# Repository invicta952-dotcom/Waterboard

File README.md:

# Waterboard
#   what is this?
this is really basic devboard with bare minmum features. it has 50 pins in total. It has an memory of 16 mb. The mcu used in this rp2040. It can only be used in simple task. It  has usb-c for flashing your firmware. It has 24 gipo pins. It has built in-clock of 12mHz

#   how to use this??
just connect the devboard with your computer and flash the code and enjoy.

#  how to assemble?
i wouldnt recommend this to you if u are an begineer, instead get it pcba
#    pcba
1) dowload the geber file from repo
2) go to jlcpcb or any other pcb service provider
3) upload the gerber
4) scroll down and select pcba
5) order it
6) enjoy

#    pcb
1) same as pcba till 3 step
2) order the pcb without pcba
3) order the components given in BOM
4) solder all the components on pcb using hot plate

#   schnematics overview

<br>
i know the schnematics is kind of messy but it is what it is

#   pcb

<br>
there are many shape i could have taken but i decided to go with dolphine because i wanted it to resemble something from minecraft which is one of my favourite game.

#   3D view

<br> 
the board kinda looks empty because i cant find cool silkscreen
<br>
<br>
#   zine

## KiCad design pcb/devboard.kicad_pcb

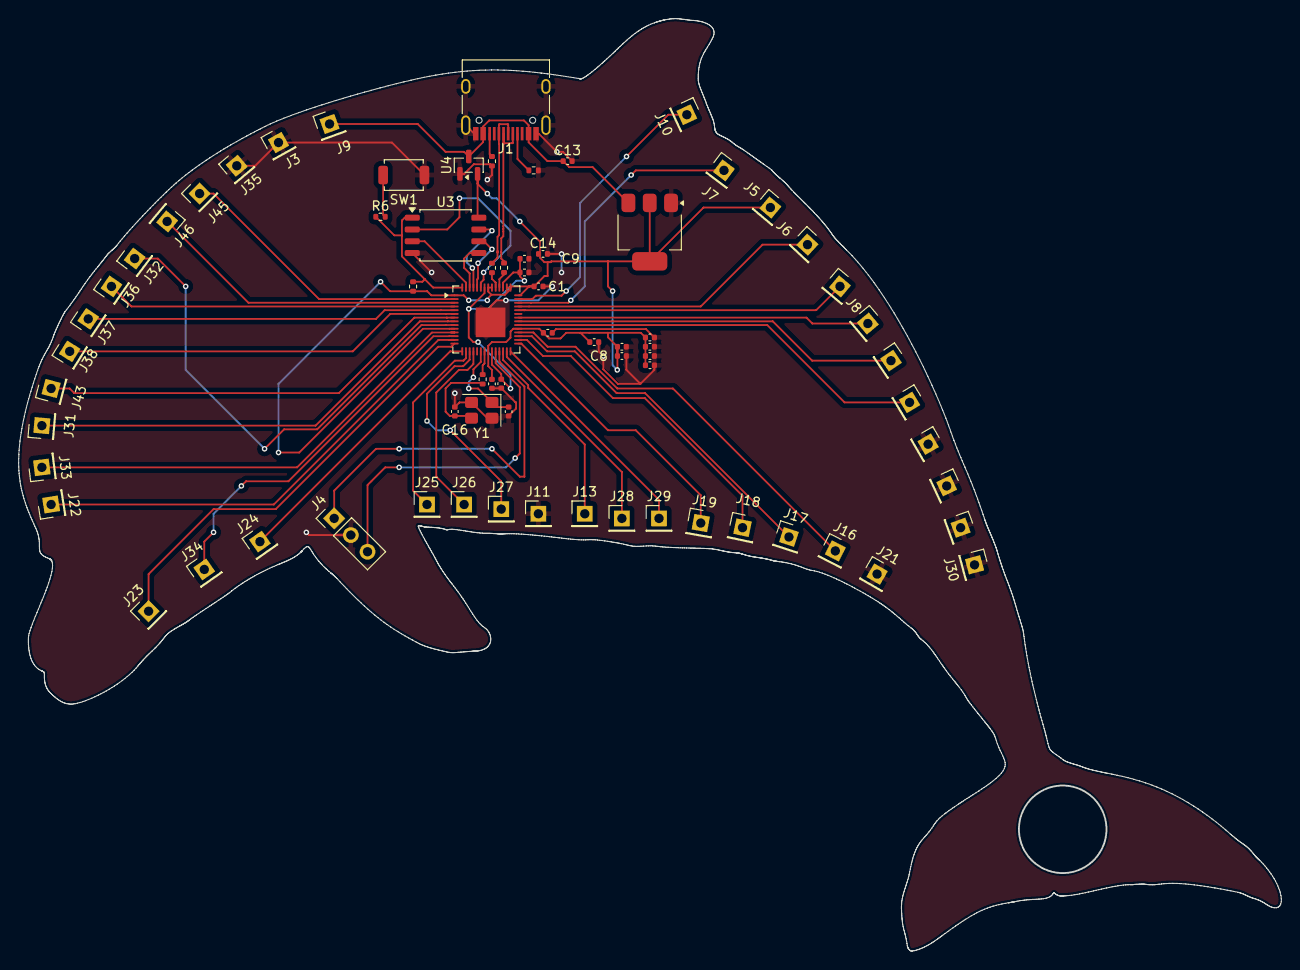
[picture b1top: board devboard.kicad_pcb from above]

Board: 2 copper layers, 135.9 x 100.3 mm, 72 parts (0 on the bottom side), 52 nets.

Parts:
C1, C2, C3, C4, C5, C6, C7, C8, C11, C12, C17: 0.1uF; C_0402_1005Metric
C9, C10: 1uF; C_0402_1005Metric
C13, C14: 10uF; C_0402_1005Metric
C15, C16: 33pF; C_0402_1005Metric
J1: USB_C_Receptacle_USB2.0_14P; USB_C_Receptacle_HRO_TYPE-C-31-M-12
J2, J3, J5, J6, J7, J8, J9, J10, J11, J12, J13, J14, J15, J16, J17, J18, J19, J20, J21, J22, J23, J24, J25, J26, J27, J28, J29, J30, J31, J32, J33, J34, J35, J36, J37, J38, J43, J44, J45, J46: Conn_01x01_Pin; PinHeader_1x01_P2.54mm_Vertical
J4: Conn_01x03_Pin; PinHeader_1x03_P2.54mm_Vertical
R1, R2: 5.1K; R_0402_1005Metric
R3, R4: 27; R_0402_1005Metric
R5, R6: 1K; R_0402_1005Metric
R7: 10K; R_0402_1005Metric
SW1: SW_Push; SW_SPST_TS-1088-xR020
U1: RP2040; QFN-56-1EP_7x7mm_P0.4mm_EP3.2x3.2mm
U2: NCP1117-3.3_SOT223; SOT-223-3_TabPin2
U3: W25Q128JVS; SOIC-8_5.3x5.3mm_P1.27mm
U4: MCP1700x-330xxTT; SOT-23
Y1: 12 MHz; Crystal_SMD_3225-4Pin_3.2x2.5mm

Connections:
+1V1: C9.1, C11.1, C12.1, U1.23 (DVDD), U1.45 (VREG_VOUT), U1.50 (DVDD)
+3V3: C1.1, C2.1, C3.1, C4.1, C5.1, C6.1, C7.1, C8.1, C10.1, C14.1, C17.2, J5.1, R7.1, U1.1 (IOVDD), U1.10 (IOVDD), U1.22 (IOVDD), U1.33 (IOVDD), U1.42 (IOVDD), U1.43 (ADC_AVDD), U1.44 (VREG_VIN), U1.48 (USB_VDD), U1.49 (IOVDD), U2.2 (VO), U3.8 (VCC), U4.2 (VO)
GIPO0: J45.1, U1.2 (GPIO0)
GIPO1: J46.1, U1.3 (GPIO1)
GIPO2: J36.1, U1.4 (GPIO2)
GIPO3: J37.1, U1.5 (GPIO3)
GIPO4: J38.1, U1.6 (GPIO4)
GIPO5: J43.1, U1.7 (GPIO5)
GIPO6: J31.1, U1.8 (GPIO6)
GIPO7: J32.1, U1.9 (GPIO7)
GIPO8: J33.1, U1.11 (GPIO8)
GIPO9: J34.1, U1.12 (GPIO9)
GIPO10: J22.1, U1.13 (GPIO10)
GIPO11: J23.1, U1.14 (GPIO11)
GIPO12: J24.1, U1.15 (GPIO12)
GIPO13: J25.1, U1.16 (GPIO13)
GIPO14: J27.1, U1.17 (GPIO14)
GIPO15: J26.1, U1.18 (GPIO15)
GIPO16: J28.1, U1.27 (GPIO16)
GIPO17: J29.1, U1.28 (GPIO17)
GIPO18: J19.1, U1.29 (GPIO18)
GIPO19: J18.1, U1.30 (GPIO19)
GIPO20: J17.1, U1.31 (GPIO20)
GIPO21: J16.1, U1.32 (GPIO21)
GIPO22: J14.1, U1.34 (GPIO22)
GIPO23: J12.1, U1.35 (GPIO23)
GIPO24: J8.1, U1.36 (GPIO24)
GIPO_ABC0: J2.1, U1.38 (GPIO26/ADC0)
GIPO_ABC1: J6.1, U1.39 (GPIO27/ADC1)
GIPO_ABC2: J7.1, U1.40 (GPIO28/ADC2)
GIPO_ABC3: J10.1, U1.41 (GPIO29/ADC3)
GND: C1.2, C2.2, C3.2, C4.2, C5.2, C6.2, C7.2, C8.2, C9.2, C10.2, C11.2, C12.2, C13.2, C14.2, C15.2, C16.2, C17.1, J1.A1 (GND), J1.A12 (GND), J1.B1 (GND), J1.B12 (GND), J1.S1 (SHIELD), J3.1, J4.2, J11.1, J15.1, J20.1, J21.1, J30.1, J35.1, J44.1, R1.1, R2.2, SW1.1, U1.57 (GND), U2.1 (GND), U3.4 (GND), U4.1 (GND), Y1.2 (G), Y1.4 (G)
unnamed: C16.1, R5.2, Y1.3
unnamed: J1.A5 (CC1), R2.1
unnamed: J1.B5 (CC2), R1.2
unnamed: R6.2, SW1.2
unnamed: R3.2, U1.46 (USB_DM)
unnamed: R4.2, U1.47 (USB_DP)
QSPI_SCLK: U1.52 (QSPI_SCLK), U3.6 (CLK)
QSPI_SD0: U1.53 (QSPI_SD0), U3.7 (~HOLD/~RESET/IO_{3})
QSPI_SD1: U1.55 (QSPI_SD1), U3.3 (~WP/IO_{2})
QSPI_SD2: U1.51 (QSPI_SD3), U3.2 (DO/IO_{1})
QSPI_SD3: U1.54 (QSPI_SD2), U3.5 (DI/IO_{0})
QSPI_SS: R6.1, R7.2, U1.56 (~QSPI_SS), U3.1 (~CS)
RUN: J13.1, U1.26 (RUN)
SWCLK: J4.3, U1.24 (SWCLK)
SWD: J4.1, U1.25 (SWDIO)
VBUS: C13.1, J1.A4 (VBUS), J1.A9 (VBUS), J1.B4 (VBUS), J1.B9 (VBUS), J9.1, U2.3 (VI), U4.3 (VI)
XIN: C15.1, U1.20 (XIN), Y1.1
XOUT: R5.1, U1.21 (XOUT)
usb_D+: J1.A6 (D+), J1.B6 (D+), R4.1
usb_D-: J1.A7 (D-), J1.B7 (D-), R3.1

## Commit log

2026-06-09 Rename waterboard.csv to BOM.csv
2026-06-09 Rename WATERBOARD.pdf to zine.pdf
